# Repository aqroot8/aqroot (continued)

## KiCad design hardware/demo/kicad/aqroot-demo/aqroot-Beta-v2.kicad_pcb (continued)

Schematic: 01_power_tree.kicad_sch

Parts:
C20: 4.7uF 10V X7R; C_0805_2012Metric; MPN CC0805KKX7R8BB475; LCSC C354262
C21, C22: 100pF DNP; C_0603_1608Metric; not fitted
C23, C58, C59: 1uF 25V X7R; C_0603_1608Metric; MPN CC0603KRX7R8BB105; LCSC C106858
C24: 10uF 25V X5R; C_0603_1608Metric; MPN GRM188R61E106KA73D; LCSC C344022
C25, C62, C63, C67: 1uF 10V X7R; C_0603_1608Metric; MPN CC0603KRX7R8BB105; LCSC C106858
C26, C27: 10uF 10V X7R; C_1206_3216Metric; MPN GRM31CR71E106KA12L; LCSC C77093
C28, C36, C60, C61, C68: 100nF X7R; C_0603_1608Metric; MPN CC0603KRX7R9BB104; LCSC C14663
C29, C30, C31, C32: 22uF 16V X7R; C_1206_3216Metric; MPN TCC1206X7R226K160HT; LCSC C22392398
C33, C64, C83, C84: 10uF 10V X7R; C_0805_2012Metric; MPN CC0805KKX7R7BB106; LCSC C326595
C34, C35: 22uF 10V X7R; C_0805_2012Metric; not fitted
C57: 4.7nF 50V X7R; C_0603_1608Metric; MPN 0603B472K500NT; LCSC C53987
C65, C66: 22uF 10V X7R; C_0805_2012Metric; MPN GRM21BZ71A226ME15L; LCSC C907991
D9: PMEG2010AEH; D_SOD-123F; MPN PMEG2010AEH,115; LCSC C110921
D10, D11, D12: BAT54WS; D_SOD-323; MPN BAT54WS-7-F; LCSC C124205
F1: 5A one-shot 1206; Fuse_1206_3216Metric; MPN 0466005.NRHF; LCSC C57525
J3: USB_C_Receptacle_USB2.0_16P; USB_C_Receptacle_GCT_USB4105-xx-A_16P_TopMnt_Horizontal; MPN USB4105-GF-A-120; LCSC C5184243
J4: BATTERY PIGTAIL 26AWG; JST_PH_B2B-PH-K_1x02_P2.00mm_Vertical; MPN D-781-BAT-PIGTAIL
L1: 1.5uH; Coilcraft_XFL4020; MPN XFL4020-152MEC; LCSC C3033018
L2: 1uH; Wurth_WE-MAPI_4030_74438357010; MPN 74438357010; LCSC C5542269; not fitted
L4: 1uH; Wurth_WE-MAPI_4030_74438357010; MPN 74438357010; LCSC C5542269
Q2, Q3: AO4800; SOIC-8_3.9x4.9mm_P1.27mm; MPN AO4800; LCSC C17098
Q4, Q6, Q7, Q8, Q9: BSS138; SOT-23; MPN BSS138LT1G; LCSC C82045
Q5: AO3401A; SOT-23; MPN AO3401A; LCSC C15127
R30, R31: 5.1k; R_0603_1608Metric; MPN 0603WAF5101T5E; LCSC C23186
R32, R35: 0R; R_0603_1608Metric; MPN 0603WAF0000T5E; LCSC C21189
R33, R34: 22R; R_0603_1608Metric; MPN 0603WAF220JT5E; LCSC C23345
R36: 13k 1%; R_0603_1608Metric; MPN 0603WAF1302T5E; LCSC C22797
R37: 390R 1%; R_0603_1608Metric; MPN 0603WAF3900T5E; LCSC C23151
R38: 10k 1%; R_0603_1608Metric; MPN 0603WAF1002T5E; LCSC C25804
R39: 1M 0.1%; R_0603_1608Metric; MPN ARG03BTC1004; LCSC C335092
R40: 189K 0.1%; R_0603_1608Metric; MPN RT0603BRD07189KL; LCSC C861174
R41, R80, R82, R94, R96: 1M; R_0603_1608Metric; MPN 0603WAF1004T5E; LCSC C22935
R43: 100K; R_0603_1608Metric; MPN 0603WAF1003T5E; LCSC C25803
R44: 732k 1%; R_0603_1608Metric; not fitted
R45: 100k 1%; R_0603_1608Metric; not fitted
R68, R107: 0R DNP; R_0603_1608Metric; not fitted
R75: 10mR 1% 3W; R_2512_6332Metric; MPN CRA2512-FZ-R010ELF; LCSC C840621
R76: 22k; R_0603_1608Metric; MPN 0603WAF2202T5E; LCSC C31850
R77, R91: 3.65M 1%; R_0603_1608Metric; MPN RC0603FR-073M65L; LCSC C482835
R78: 442k 1%; R_0603_1608Metric; MPN RC0603FR-07442KL; LCSC C185327
R79: 510k; R_0603_1608Metric; MPN 0603WAF5103T5E; LCSC C23192
R81, R98, R102, R103: 100k; R_0603_1608Metric; MPN 0603WAF1003T5E; LCSC C25803
R83: 10k; R_0603_1608Metric; MPN 0603WAF1002T5E; LCSC C25804
R84: 100R; R_0603_1608Metric; MPN 0603WAF1000T5E; LCSC C22775
R85, R86, R87, R88, R89, R90: 2.2M 1%; R_0603_1608Metric; MPN RC0603FR-072M2L; LCSC C137747
R92: 1.30M 1%; R_0603_1608Metric; MPN MCT06030C1304FP500; LCSC C2115863
R93: 22M DNP; R_0603_1608Metric; not fitted
R95: 560R 1% 1206; R_1206_3216Metric; MPN ERJ-P08F5600V; LCSC C4220370
R97: 1.87k 1%; R_0603_1608Metric; MPN 0603WAF1871T5E; LCSC C22850
R99: 732k 1%; R_0603_1608Metric; MPN CRCW0603732KFKEA; LCSC C2079739
R100: 100k 1%; R_0603_1608Metric; MPN 0603WAF1003T5E; LCSC C25803
R101: 2.43k 1%; R_0603_1608Metric; MPN 0603WAF2431T5E; LCSC C22906
R104: 150k 1%; R_0603_1608Metric; MPN 0603WAF1503T5E; LCSC C22807
R105: 220k 1%; R_0603_1608Metric; MPN 0603WAF2203T5E; LCSC C22961
R106: 0R FIT; R_0603_1608Metric; MPN 0603WAF0000T5E; LCSC C21189
R131: 100k; R_0603_1608Metric; Tolerance 1%; MPN 0603WAF1003T5E; LCSC C25803
SW9: SW_SPDT; SW_SPDT_CK_JS102011SAQN; MPN JS102011SAQN; LCSC C221660
TP6, TP7, TP8, TP9, TP10, TP11, TP13, TP15, TP16, TP17, TP18, TP19, TP20, TP21, TP22, TP23, TP24, TP25, TP26, TP27, TP28, TP29, TP30, TP31, TP32, TP33, TP34, TP47: TestPoint; TestPoint_Pad_D1.0mm
U10: USBLC6-2SC6; SOT-23-6; MPN USBLC6-2SC6; LCSC C7519
U11: BQ25185; Texas_DLH0010A_WSON-10-1EP_2.2x2mm_P0.4mm_EP0.9x1.5mm; MPN BQ25185DLHR; LCSC C19725033
U12: TPS63020; TI_TPS63020_DSJ; MPN TPS63020DSJR; LCSC C15483
U13: TPS61023; SOT-563; MPN TPS61023DRLR; LCSC C919459; not fitted
U14: MAX17048; MAX17048_T822; MPN MAX17048G+T10; LCSC C2682616
U18: LTC4368-1; MSOP-10_3x3mm_P0.5mm; MPN LTC4368IMS-1#TRPBF; LCSC C688401
U19: TLV7032; SOT-23-8; MPN TLV7032DDFR; LCSC C2871498
U20, U22: TPS22950-Q1; SOT-23-6; MPN TPS22950CQDDCRQ1; LCSC C17349276
U21: TPS61023; SOT-563; MPN TPS61023DRLR; LCSC C919459

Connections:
+3V3: C29.1, C30.1, C31.1, C32.1, C62.1, R39.1, R41.1, R81.1, R103.1, R106.1, U12.4 (VOUT), U12.5 (VOUT), U20.2 (VIN); also elsewhere on the board
/01_POWER_TREE/ACC_3V3_ILIM: R97.1, U20.4 (ILIM)
/01_POWER_TREE/ACC_5V_FB: R99.2, R100.1, U21.1 (FB)
/01_POWER_TREE/ACC_5V_ILIM: R101.1, U22.4 (ILIM)
/01_POWER_TREE/ACC_5V_LX: L4.2, U21.5 (SW)
/01_POWER_TREE/ACC_5V_RAW: C65.1, C66.1, R99.1, TP28.1, U21.6 (VOUT), U22.2 (VIN)
/01_POWER_TREE/BAT_CONNECTOR_P: F1.1, J4.1, TP34.1
/01_POWER_TREE/BAT_MID: Q2.5 (D2), Q2.6 (D2), Q3.7 (D1), Q3.8 (D1)
/01_POWER_TREE/BAT_PROTECTED_P: C25.1, C36.1, C58.1, D9.1 (K), R75.2, TP15.1, U11.2 (BAT), U14.2 (CELL), U14.3 (VDD), U18.8 (VOUT)
/01_POWER_TREE/BAT_PROT_SHDN_CTL: Q4.1 (G), R83.1, TP19.1
/01_POWER_TREE/BAT_RAW: C59.1, D12.1 (K), F1.2, Q2.7 (D1), Q2.8 (D1), R77.1, R79.1, R80.1, R86.2, R89.1, TP16.1, U18.1 (VIN)
/01_POWER_TREE/BAT_SENSE: Q3.5 (D2), Q3.6 (D2), R75.1, TP20.1, U18.9 (SENSE)
/01_POWER_TREE/BQ25185_SYS: C24.1, C26.2, C27.1, C28.1, C33.1, C64.1, C83.1, C84.1, L2.1, L4.1, R68.1, SW9.2 (B), U11.1 (SYS), U12.1 (VINA), U12.10 (VIN), U12.11 (VIN), U13.3 (VIN), U21.3 (VIN)
/01_POWER_TREE/ILIM_VSET: R36.1, U11.7 (ILIM_VSET)
/01_POWER_TREE/ISET: R37.1, U11.8 (ISET)
/01_POWER_TREE/LTC4368_FAULT_N: Q9.1 (G), R81.2, R82.1, TP18.1, U18.7 (~FAULT)
/01_POWER_TREE/LTC_GATE: Q2.2 (G1), Q2.4 (G2), Q3.2 (G1), Q3.4 (G2), R76.1, TP17.1, U18.10 (GATE)
/01_POWER_TREE/LTC_GATE_RC: C57.1, R76.2
/01_POWER_TREE/LTC_OV: R77.2, R78.1, U18.3 (OV)
/01_POWER_TREE/LTC_SHDN: Q4.3 (D), R80.2, U18.6 (~SHDN)
/01_POWER_TREE/LTC_UV: R79.2, U18.2 (UV)
/01_POWER_TREE/MAX17048_ALRT_N: TP11.1, U14.5 (~ALRT)
/01_POWER_TREE/NFC_5V_PA_PENDING: C34.2, C35.1, R44.2, R107.1, TP9.1, U13.6 (VOUT)
/01_POWER_TREE/N_BATDIV: C61.1, R89.2, R90.1, U19.6 (INB-)
/01_POWER_TREE/N_POL: R85.2, R86.1, TP23.1, U19.3 (INA+)
/01_POWER_TREE/Q2_CS: Q2.1 (S1), Q2.3 (S2)
/01_POWER_TREE/Q3_CS: Q3.1 (S1), Q3.3 (S2)
/01_POWER_TREE/REC_AND1: Q6.2 (S), Q7.3 (D)
/01_POWER_TREE/REC_AND2: Q7.2 (S), Q8.3 (D)
/01_POWER_TREE/REC_BAT_LOW: Q7.1 (G), R93.1, U19.7 (OUTB)
/01_POWER_TREE/REC_DIODE_IN: D12.2 (A), R95.2, TP22.1
/01_POWER_TREE/REC_FAULT_B: Q8.1 (G), Q9.3 (D), R96.2
/01_POWER_TREE/REC_GATE_N: Q5.1 (G), Q6.3 (D), R94.2, TP21.1
/01_POWER_TREE/REC_LIM_IN: Q5.3 (D), R95.1
/01_POWER_TREE/REC_POL_OK: Q6.1 (G), U19.1 (OUTA)
/01_POWER_TREE/REF_HO: R91.2, R92.1, R93.2, U19.5 (INB+)
/01_POWER_TREE/REF_POL: R87.2, R88.1, TP24.1, U19.2 (INA-)
/01_POWER_TREE/USB_D_CONN_N: J3.A7 (D-), J3.B7 (D-), U10.1 (I/O1)
/01_POWER_TREE/USB_D_CONN_P: J3.A6 (D+), J3.B6 (D+), U10.3 (I/O2)
/01_POWER_TREE/USB_D_ESD_N: R33.1, U10.6 (I/O1)
/01_POWER_TREE/USB_D_ESD_P: R34.1, U10.4 (I/O2)
/01_POWER_TREE/USB_VBUS_CHG: C23.2, D10.2 (A), D11.2 (A), Q5.2 (S), R35.2, R84.1, R91.1, R94.1, R96.1, R104.1, U11.10 (IN)
/01_POWER_TREE/USB_VBUS_RAW: C20.1, J3.A4 (VBUS), J3.A9 (VBUS), J3.B4 (VBUS), J3.B9 (VBUS), R35.1, U10.5 (VBUS)
/01_POWER_TREE/V3V3_FB: R39.2, R40.1, U12.3 (FB)
/01_POWER_TREE/VBRIDGE_TOP: D10.1 (K), R85.1
/01_POWER_TREE/VBUS_PRESENT: C68.1, R104.2, R105.1, TP31.1
/01_POWER_TREE/VREC_VCC: C60.1, R84.2, U19.8 (VCC)
/01_POWER_TREE/VREF_TOP: D11.1 (K), R87.1
/ACC_3V3_EN: R98.1, TP26.1, U20.1 (ON); also elsewhere on the board
/ACC_3V3_SW: C63.1, TP25.1, U20.5 (VOUT); also elsewhere on the board
/ACC_5V_BOOST_EN: R102.1, TP30.1, U21.2 (EN); also elsewhere on the board
/ACC_5V_SW: C67.1, TP29.1, U22.5 (VOUT); also elsewhere on the board
/ACC_5V_SW_EN: R131.1, TP47.1, U22.1 (ON); also elsewhere on the board
/ACC_POWER_FAULT_N: R103.2, TP27.1, TP33.1, U20.6 (~FLT), U22.6 (~FLT); also elsewhere on the board
/BQ25185_STAT1: TP6.1, U11.9 (STAT1); also elsewhere on the board
/BQ25185_STAT2: TP7.1, U11.3 (STAT2); also elsewhere on the board
/I2C_SCL_INT: U14.7 (SCL); also elsewhere on the board
/I2C_SDA_INT: U14.8 (SDA); also elsewhere on the board
/NFC_5V_EN: TP10.1, U13.2 (EN); also elsewhere on the board
/NFC_SUPPLY: R106.2, R107.2, TP32.1; also elsewhere on the board
/USB_D_MCU_N: R33.2; also elsewhere on the board
/USB_D_MCU_P: R34.2; also elsewhere on the board
GND: C20.2, C21.2, C22.2, C23.1, C24.2, C25.2, C26.1, C27.2, C28.2, C29.2, C30.2, C31.2, C32.2, C33.2, C34.1, C35.2, C36.2, C57.2, C58.2, C59.2, C60.2, C61.2, C62.2, C63.2, C64.2, C65.2, C66.2, C67.2, C68.2, C83.2, C84.2, D9.2 (A), J3.A1 (GND), J3.A12 (GND), J3.B1 (GND), J3.B12 (GND), J4.2, Q4.2 (S), Q8.2 (S), Q9.2 (S), R30.2, R31.2, R32.2, R36.2, R37.2, R38.2, R40.2, R43.2, R45.2, R78.2, R82.2, R83.2, R88.2, R90.2, R92.2, R97.2, R98.2, R100.2, R101.2, R102.2, R105.2, R131.2, U10.2 (GND), U11.4 (~CE), U11.5 (GND), U11.11 (EP), U12.2 (GND), U12.15 (PGND_EP), U13.4 (GND), U14.1 (CTG), U14.4 (GND), U14.6 (QSTRT), U14.9 (EP), U18.4 (RETRY), U18.5 (GND), U19.4 (VEE), U20.3 (GND), U21.4 (GND), U22.3 (GND); also elsewhere on the board
unnamed: J3.A5 (CC1), R31.1
unnamed: J3.B5 (CC2), R30.1
unnamed: J3.SH (SHIELD), R32.1
unnamed: L1.1, U12.8 (L1), U12.9 (L1)
unnamed: L1.2, U12.6 (L2), U12.7 (L2)
unnamed: R43.1, R68.2, SW9.1 (A), TP13.1, U12.12 (EN), U12.13 (PS_SYNC)
unnamed: R38.1, U11.6 (TS_MR)
unnamed: R41.2, TP8.1, U12.14 (PG)
unnamed: R44.1, R45.1, U13.1 (FB)
unnamed: L2.2, U13.5 (SW)

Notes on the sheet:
MAX17048 FUEL GAUGE I2C ADDRESS 0x36 NO SENSE RESISTOR NEVER BENCH VALIDATED ON AQROOT BETA BRING-UP REQUIRED VERIFY: CELL VOLTAGE SOC PLAUSIBILITY HIBERNATE BATTERY INSERTION / REMOVAL NO I2C BACKPOWER DURING +3V3 HARD-OFF FOOTPRINT PENDING EXACT ADI LAND-PATTERN REVIEW DO NOT ROUTE UNTIL FOOTPRIN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
REVERSE-POLARITY PROTECTION - IMPLEMENTED (FBV2-S1) D-050 / D-052 / D-064 / D-068. The placeholder is RETIRED. See block A, lower left, for the captured circuit: BAT_CONNECTOR_P -> F1 -> BAT_RAW -> Q2 -> BAT_MID -> Q3 -> BAT_SENSE -> R75 10mR -> BAT_PROTECTED_P -> U11 BAT Controller U18 LTC4368-1. 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
TPS61023 NFC 5V PA BOOST DEFAULT OFF ENABLE FROM TCA9535 U60 P02 OUTPUT FEEDS ST25R3916 VDD_PA ONLY VDD_IO REMAINS +3V3 EXACT PASSIVE MPNs PENDING BOM PASS
CAPACITOR MPNs NOT BOM-LOCKED COUT: 4 x 22uF, 10V, X7R, 1206 REQUIRE COMBINED EFFECTIVE COUT >=40uF AT 3.3V VERIFY DC-BIAS / LIFECYCLE / STOCK BEFORE FAB
01_POWER_TREE - CAPTURED (FBV2-S1 POWER-TREE IMPLEMENTATION) CAPTURED: USB-C 5V SINK / USB 2.0 BQ25185 CHARGER / POWER PATH TPS63020 MAIN +3V3 RAIL TPS61023 NFC 5V PA BOOST MAX17048 FUEL GAUGE PHYSICAL MAIN-RAIL HARD OFF BATTERY REVERSE PROTECTION P2 + LTC4368-1 AUTONOMOUS DEAD-CELL RECOVERY (CANDI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
KEEP FB TRACE SHORT ROUTE AWAY FROM L1/L2 SWITCH NODES SENSE VOUT AFTER OUTPUT CAPACITORS
CIN MPNs NOT BOM-LOCKED REQUIRE COMBINED EFFECTIVE CIN >=10uF AT 4.5V VERIFY DC-BIAS / LIFECYCLE / STOCK BEFORE FAB
KEYED JST-PH BATTERY CONNECTOR PIN 1 = BAT+ PIN 2 = GND VERIFY CABLE POLARITY BEFORE CONNECTION MECHANICAL KEYING IS AN ADDITIONAL SAFEGUARD ONLY
R_PS_DEFAULT 0R DEFAULT: POWER-SAVE MODE NO GPIO
PHYSICAL MAIN-RAIL HARD OFF SWITCH OPEN: TPS63020 OFF, +3V3 OFF SWITCH CLOSED: TPS63020 ON UPSTREAM BQ25185 / MAX17048 REMAIN POWERED NOT A GPIO
L_NFC_BOOST 1uH SHIELDED EXACT MPN / ISAT / DCR PENDING BOM PASS
AO3400A-CLASS NFETs PROVISIONAL AO3401A PMOS ALTERNATIVE BUILDING BLOCK ONLY KEYED CONNECTOR IS NOT THE PRIMARY ELECTRICAL DEFENSE
R_PG_PULLUP 1M PG DIAGNOSTIC ONLY - NO GPIO
BETA: FIXED TS BIAS - NO BATTERY NTC PRODUCTION BATTERY TEMPERATURE SENSING REVIEW
C21/C22 data-side pins intentionally NC for Beta (CTO ruling, USB uncoupled budget). Populate via rework jumper only. Restore connection at next revision if Beta EMI data justifies.
=== FBV2-S1 POWER TREE :: A. BATTERY REVERSE PROTECTION (P2) - D-050 / D-052 / D-064 / D-068 ===
JST J4 -> F1 (5A backstop) -> BAT_RAW -> Q2 (stage 1, 2 FETs) -> BAT_MID -> Q3 (stage 2, 2 FETs) -> BAT_SENSE -> R75 10mR (D-771; was 15mR) -> BAT_PROTECTED_P -> BQ25185 BAT.
LTC4368-1 ONLY (the -2 trips at -3 mV and blocks charging). RETRY grounded = latch-off; SHDN toggled low-then-high clears it. D-771 FORWARD BREAKER, OVER TOLERANCE: ADI Rev C guarantees dVSENSE,F as 40 / 50 / 60 mV over temperature -- 50 mV is a TYPICAL. R75 is 10 mOhm (was 15), so the breaker trip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
=== B. AUTONOMOUS DEAD-CELL RECOVERY (Candidate B, D-065) - USB-POWERED, FIRMWARE-INDEPENDENT ===
Ratiometric polarity bridge (trip at V_BAT = 0, supply-independent) + handoff comparator + LTC4368 FAULT = hardware 3-input AND. Matched Schottkys D10/D11 keep the bridge ratiometric AND block battery drain when USB is absent.
Q6/Q7/Q8 in series form the AND. Q9 inverts FAULT (active-low) so FAULT-ASSERTED becomes a positive enable. Recovery current = (VBUS - Vf) / R95; single-fault ceiling into a reversed cell = (VBUS - Vf + 4.2) / R95. R95 = 560R LOCKED (P-20, D-105): 8.4 mA nominal at VBUS 5.0 V into a 0 V pack (7.9-8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
=== C. COMMUNITY ACCESSORY POWER (D-086 / D-087 / D-088) - ONE TPS22950-Q1 MPN ON BOTH RAILS (D-765), FLT WIRE-OR (D-094) ===
ACC_3V3: +3V3 -> TPS22950-Q1 -> ACC_3V3_SW. R_ILIM 1.78k ~ 0.636 A typ, 0.428 A GUARANTEED / 0.849 A worst case (D-771; was 2.7k at D-753). There is no accessory current measurement, so the LIMITER is the envelope and the GUARANTEE is the published figure -- and D-098 PUBLISHES 400 mA TOTAL for thi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
ACC_5V: BQ25185_SYS -> dedicated TPS61023 (5.0 V) -> dedicated TPS22950-Q1 -> ACC_5V_SW. R_ILIM 2.32k ~ 0.479 A typ, 0.322 A GUARANTEED / 0.639 A worst case (D-771; was 2.7k at D-753), against the 300 mA TOTAL D-098 PUBLISHES for this rail across BOTH its J5 contacts. NOT USB VBUS. NOT the NFC fall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
=== E. TELEMETRY + NFC NO-RESPIN SOURCE SELECT (D-055 / D-056) ===
VBUS_PRESENT: divided to 2.973 V at VBUS 5.0 V by R104 150k / R105 220k, filtered by C68. *** D-776 CORRECTED THE SECOND HALF OF THIS SENTENCE. It read 'raw VBUS NEVER reaches the expander', which reads as though the DIVIDED level does. IT DOES NOT: this node reaches TP31 and nothing else. The divi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
D-788 / R7-D787-01: PS/SYNC IS TIED TO EN, NOT TO GND. TI SLVS916I 7.4.4 -- PS/SYNC low ENABLES power save, and the EC table gives VFB_PS as 0.6 % .. 5 % ABOVE VFB_PWM. On this board that put the +3V3 rail as high as 3.542 V, against the ILI9488 panel's ABSOLUTE MAXIMUM of 3.3 V on VCI and IOVCC (v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

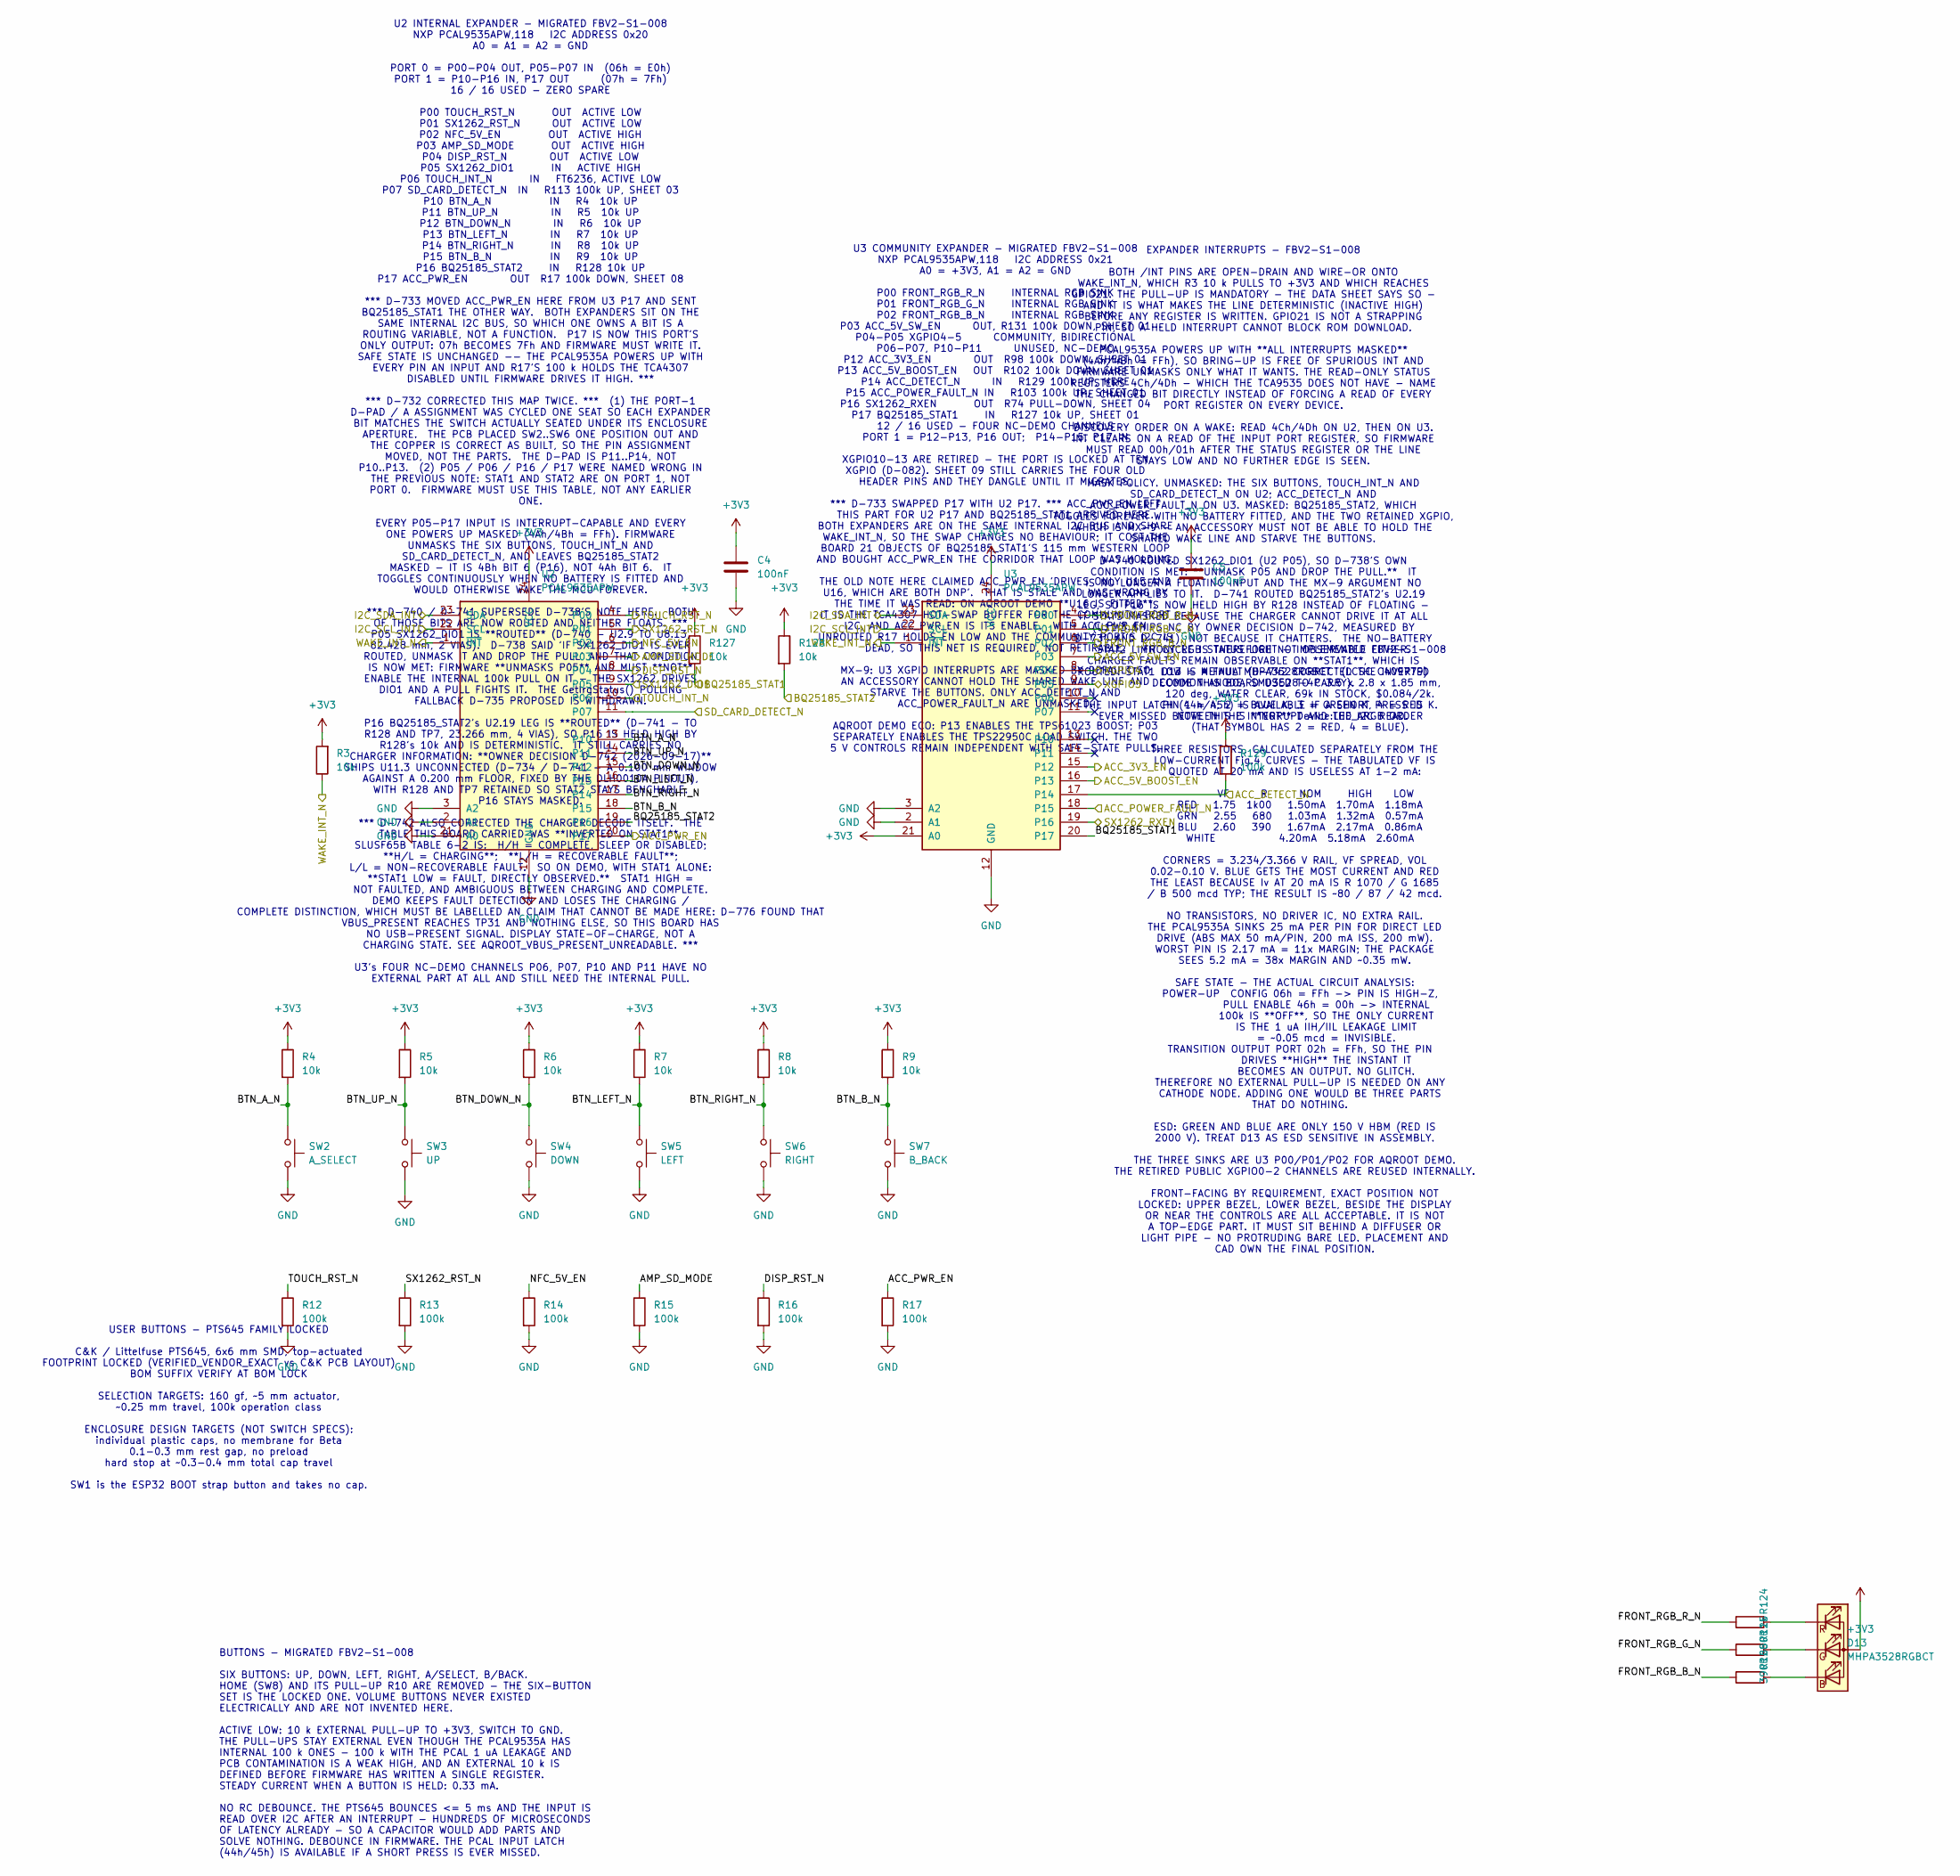
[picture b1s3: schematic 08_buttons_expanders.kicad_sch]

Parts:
C4, C5: 100nF; C_0603_1608Metric; MPN CC0603KRX7R9BB104; LCSC C14663
D13: MHPA3528RGBCT; MEIHUA_MHPA3528RGBCT_PLCC4_3.5x2.8mm; MPN MHPA3528RGBCT; LCSC C409779
R3, R4, R5, R6, R7, R8, R9: 10k; R_0603_1608Metric; MPN 0603WAF1002T5E; LCSC C25804
R12, R13, R14, R15, R16, R17: 100k; R_0603_1608Metric; MPN 0603WAF1003T5E; LCSC C25803
R124: 1k; R_0603_1608Metric; Tolerance 1%; MPN 0603WAF1001T5E; LCSC C21190
R125: 680R; R_0603_1608Metric; Tolerance 1%; MPN 0603WAF6800T5E; LCSC C23228
R126: 390R; R_0603_1608Metric; Tolerance 1%; MPN 0603WAF3900T5E; LCSC C23151
R127, R128: 10k; R_0603_1608Metric; Tolerance 1%; MPN 0603WAF1002T5E; LCSC C25804
R129: 100k; R_0603_1608Metric; Tolerance 1%; MPN 0603WAF1003T5E; LCSC C25803
SW2: A_SELECT; SW_SPST_PTS645Sx43SMTR92; MPN PTS645SM43SMTR92LFS; LCSC C221880
SW3: UP; SW_SPST_PTS645Sx43SMTR92; MPN PTS645SM43SMTR92LFS; LCSC C221880
SW4: DOWN; SW_SPST_PTS645Sx43SMTR92; MPN PTS645SM43SMTR92LFS; LCSC C221880
SW5: LEFT; SW_SPST_PTS645Sx43SMTR92; MPN PTS645SM43SMTR92LFS; LCSC C221880
SW6: RIGHT; SW_SPST_PTS645Sx43SMTR92; MPN PTS645SM43SMTR92LFS; LCSC C221880
SW7: B_BACK; SW_SPST_PTS645Sx43SMTR92; MPN PTS645SM43SMTR92LFS; LCSC C221880
U2, U3: PCAL9535APW; TSSOP-24_4.4x7.8mm_P0.65mm; MPN PCAL9535APW,118; LCSC C2669683

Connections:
+3V3: C4.1, C5.1, D13.1 (A), R3.2, R4.1, R5.1, R6.1, R7.1, R8.1, R9.1, R127.1, R128.1, R129.1, U2.24 (VCC), U3.21 (A0), U3.24 (VCC); also elsewhere on the board
/08_BUTTONS_EXPANDERS/BTN_A_N: R4.2, SW2.1, U2.13 (P10)
/08_BUTTONS_EXPANDERS/BTN_B_N: R9.2, SW7.1, U2.18 (P15)
/08_BUTTONS_EXPANDERS/BTN_DOWN_N: R6.2, SW4.1, U2.15 (P12)
/08_BUTTONS_EXPANDERS/BTN_LEFT_N: R7.2, SW5.1, U2.16 (P13)
/08_BUTTONS_EXPANDERS/BTN_RIGHT_N: R8.2, SW6.1, U2.17 (P14)
/08_BUTTONS_EXPANDERS/BTN_UP_N: R5.2, SW3.1, U2.14 (P11)
/08_BUTTONS_EXPANDERS/FRONT_RGB_B_N: R126.1, U3.6 (P02)
/08_BUTTONS_EXPANDERS/FRONT_RGB_G_N: R125.1, U3.5 (P01)
/08_BUTTONS_EXPANDERS/FRONT_RGB_R_N: R124.1, U3.4 (P00)
/ACC_3V3_EN: U3.15 (P12); also elsewhere on the board
/ACC_5V_BOOST_EN: U3.16 (P13); also elsewhere on the board
/ACC_5V_SW_EN: U3.7 (P03); also elsewhere on the board
/ACC_DETECT_N: R129.2, U3.17 (P14); also elsewhere on the board
/ACC_POWER_FAULT_N: U3.18 (P15); also elsewhere on the board
/ACC_PWR_EN: R17.1, U2.20 (P17); also elsewhere on the board
/AMP_SD_MODE: R15.1, U2.7 (P03); also elsewhere on the board
/BQ25185_STAT1: R127.2, U3.20 (P17); also elsewhere on the board
/BQ25185_STAT2: R128.2, U2.19 (P16); also elsewhere on the board
/DISP_RST_N: R16.1, U2.8 (P04); also elsewhere on the board
/I2C_SCL_INT: U2.22 (SCL), U3.22 (SCL); also elsewhere on the board
/I2C_SDA_INT: U2.23 (SDA), U3.23 (SDA); also elsewhere on the board
/NFC_5V_EN: R14.1, U2.6 (P02); also elsewhere on the board
/SD_CARD_DETECT_N: U2.11 (P07); also elsewhere on the board
/SX1262_DIO1: U2.9 (P05); also elsewhere on the board
/SX1262_RST_N: R13.1, U2.5 (P01); also elsewhere on the board
/SX1262_RXEN: U3.19 (P16); also elsewhere on the board
/TOUCH_INT_N: U2.10 (P06); also elsewhere on the board
/TOUCH_RST_N: R12.1, U2.4 (P00); also elsewhere on the board
/WAKE_INT_N: R3.1, U2.1 (~INT), U3.1 (~INT); also elsewhere on the board
/XGPIO4: U3.8 (P04); also elsewhere on the board
/XGPIO5: U3.9 (P05); also elsewhere on the board
GND: C4.2, C5.2, R12.2, R13.2, R14.2, R15.2, R16.2, R17.2, SW2.2, SW3.2, SW4.2, SW5.2, SW6.2, SW7.2, U2.2 (A1), U2.3 (A2), U2.12 (GND), U2.21 (A0), U3.2 (A1), U3.3 (A2), U3.12 (GND); also elsewhere on the board
unnamed: D13.2 (BK), R126.2
unnamed: D13.3 (GK), R125.2
unnamed: D13.4 (RK), R124.2

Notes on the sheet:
USER BUTTONS - PTS645 FAMILY LOCKED C&K / Littelfuse PTS645, 6x6 mm SMD, top-actuated FOOTPRINT LOCKED (VERIFIED_VENDOR_EXACT vs C&K PCB LAYOUT) BOM SUFFIX VERIFY AT BOM LOCK SELECTION TARGETS: 160 gf, ~5 mm actuator, ~0.25 mm travel, 100k operation class ENCLOSURE DESIGN TARGETS (NOT SWITCH SPECS)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
BUTTONS - MIGRATED FBV2-S1-008 SIX BUTTONS: UP, DOWN, LEFT, RIGHT, A/SELECT, B/BACK. HOME (SW8) AND ITS PULL-UP R10 ARE REMOVED - THE SIX-BUTTON SET IS THE LOCKED ONE. VOLUME BUTTONS NEVER EXISTED ELECTRICALLY AND ARE NOT INVENTED HERE. ACTIVE LOW: 10 k EXTERNAL PULL-UP TO +3V3, SWITCH TO GND. THE 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
U2 INTERNAL EXPANDER - MIGRATED FBV2-S1-008 NXP PCAL9535APW,118 I2C ADDRESS 0x20 A0 = A1 = A2 = GND PORT 0 = P00-P04 OUT, P05-P07 IN (06h = E0h) PORT 1 = P10-P16 IN, P17 OUT (07h = 7Fh) 16 / 16 USED - ZERO SPARE P00 TOUCH_RST_N OUT ACTIVE LOW P01 SX1262_RST_N OUT ACTIVE LOW P02 NFC_5V_EN OUT ACTIVE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
U3 COMMUNITY EXPANDER - MIGRATED FBV2-S1-008 NXP PCAL9535APW,118 I2C ADDRESS 0x21 A0 = +3V3, A1 = A2 = GND P00 FRONT_RGB_R_N INTERNAL RGB SINK P01 FRONT_RGB_G_N INTERNAL RGB SINK P02 FRONT_RGB_B_N INTERNAL RGB SINK P03 ACC_5V_SW_EN OUT, R131 100k DOWN, SHEET 01 P04-P05 XGPIO4-5 COMMUNITY, BIDIRECTI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
FRONT RGB STATUS LIGHT - IMPLEMENTED FBV2-S1-008 D13 = MEIHUA MHPA3528RGBCT (LCSC C409779) COMMON ANODE, SMD3528-4P 3.5 x 2.8 x 1.85 mm, 120 deg, WATER CLEAR, 69k IN STOCK, $0.084/2k. PIN 1 = A, 2 = BLUE K, 3 = GREEN K, 4 = RED K. NOTE THIS IS **NOT** Device:LED_ARGB ORDER (THAT SYMBOL HAS 2 = RED,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
EXPANDER INTERRUPTS - FBV2-S1-008 BOTH /INT PINS ARE OPEN-DRAIN AND WIRE-OR ONTO WAKE_INT_N, WHICH R3 10 k PULLS TO +3V3 AND WHICH REACHES GPIO21. THE PULL-UP IS MANDATORY - THE DATA SHEET SAYS SO - AND IT IS WHAT MAKES THE LINE DETERMINISTIC (INACTIVE HIGH) BEFORE ANY REGISTER IS WRITTEN. GPIO21 I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

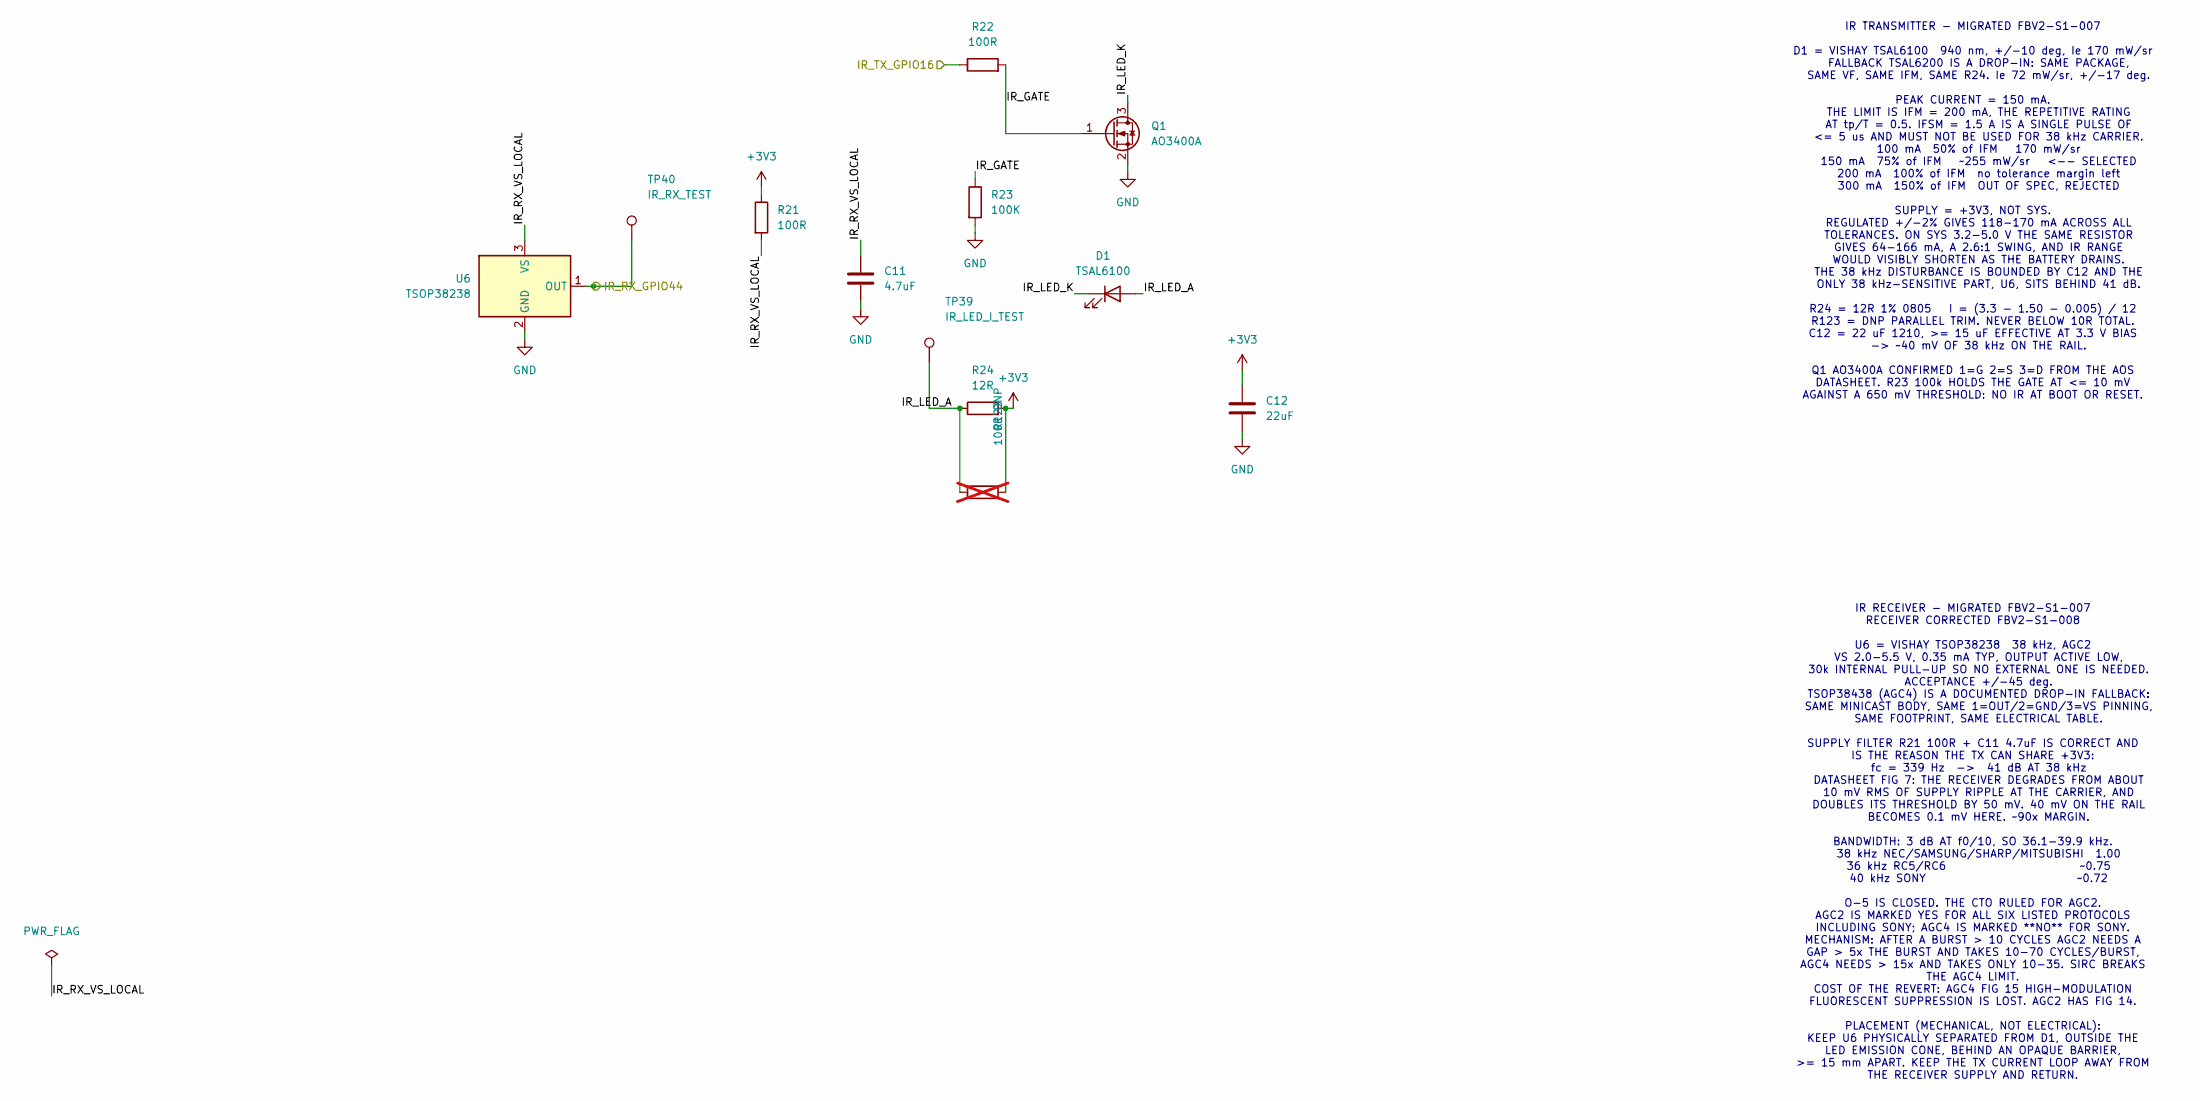
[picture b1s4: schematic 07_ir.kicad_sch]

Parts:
C11: 4.7uF; C_0805_2012Metric; MPN CL21A475KAQNNNE; LCSC C1779
C12: 22uF; C_1210_3225Metric; Voltage 16V; MPN CL32B226KAJNNNE; LCSC C309062
D1: TSAL6100; LED_D5.0mm; MPN TSAL6100; LCSC C111836
Q1: AO3400A; SOT-23; MPN AO3400A; LCSC C20917
R21, R22: 100R; R_0603_1608Metric; MPN 0603WAF1000T5E; LCSC C22775
R23: 100K; R_0603_1608Metric; MPN 0603WAF1003T5E; LCSC C25803
R24: 12R; R_0805_2012Metric; Tolerance 1%; MPN SR0805FR-4712RL; LCSC C26080556
R123: 100R DNP; R_0805_2012Metric; not fitted
TP39: IR_LED_I_TEST; TestPoint_Pad_D1.0mm
TP40: IR_RX_TEST; TestPoint_Pad_D1.0mm
U6: TSOP38238; Vishay_TSOP382xx_Minicast_3Pin_P2.54mm; MPN TSOP38238; LCSC C141632

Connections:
+3V3: C12.2, R21.1, R24.2, R123.2; also elsewhere on the board
/07_IR/IR_GATE: Q1.1 (G), R22.2, R23.1
/07_IR/IR_LED_A: D1.2 (A), R24.1, R123.1, TP39.1
/07_IR/IR_LED_K: D1.1 (K), Q1.3 (D)
/07_IR/IR_RX_VS_LOCAL: C11.1, R21.2, U6.3 (VS)
/IR_RX_GPIO44: TP40.1, U6.1 (OUT); also elsewhere on the board
/IR_TX_GPIO16: R22.1; also elsewhere on the board
GND: C11.2, C12.1, Q1.2 (S), R23.2, U6.2 (GND); also elsewhere on the board

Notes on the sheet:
IR TRANSMITTER - MIGRATED FBV2-S1-007 D1 = VISHAY TSAL6100 940 nm, +/-10 deg, Ie 170 mW/sr FALLBACK TSAL6200 IS A DROP-IN: SAME PACKAGE, SAME VF, SAME IFM, SAME R24. Ie 72 mW/sr, +/-17 deg. PEAK CURRENT = 150 mA. THE LIMIT IS IFM = 200 mA, THE REPETITIVE RATING AT tp/T = 0.5. IFSM = 1.5 A IS A SING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
IR RECEIVER - MIGRATED FBV2-S1-007 RECEIVER CORRECTED FBV2-S1-008 U6 = VISHAY TSOP38238 38 kHz, AGC2 VS 2.0-5.5 V, 0.35 mA TYP, OUTPUT ACTIVE LOW, 30k INTERNAL PULL-UP SO NO EXTERNAL ONE IS NEEDED. ACCEPTANCE +/-45 deg. TSOP38438 (AGC4) IS A DOCUMENTED DROP-IN FALLBACK: SAME MINICAST BODY, SAME 1=O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
